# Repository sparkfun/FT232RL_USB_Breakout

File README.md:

FT232RL USB Breakout
====================

[
*FT232RL USB to Serial Breakout Board (BOB-00718)*](https://www.sparkfun.com/products/718)

This is a basic breakout board for FTDI's popular USB to UART IC.
VCCIO is tied to 3.3V through a solder jumper. 

Repository Contents
-------------------
* **/Hardware** - All Eagle design files (.brd, .sch)

License Information
-------------------
The hardware is released under [Creative Commons Share-alike 3.0](http://creativecommons.org/licenses/by-sa/3.0/).  
All other code is open source so please feel free to do anything you want with it; you buy me a beer if you use this and we meet someday ([Beerware license](http://en.wikipedia.org/wiki/Beerware)).

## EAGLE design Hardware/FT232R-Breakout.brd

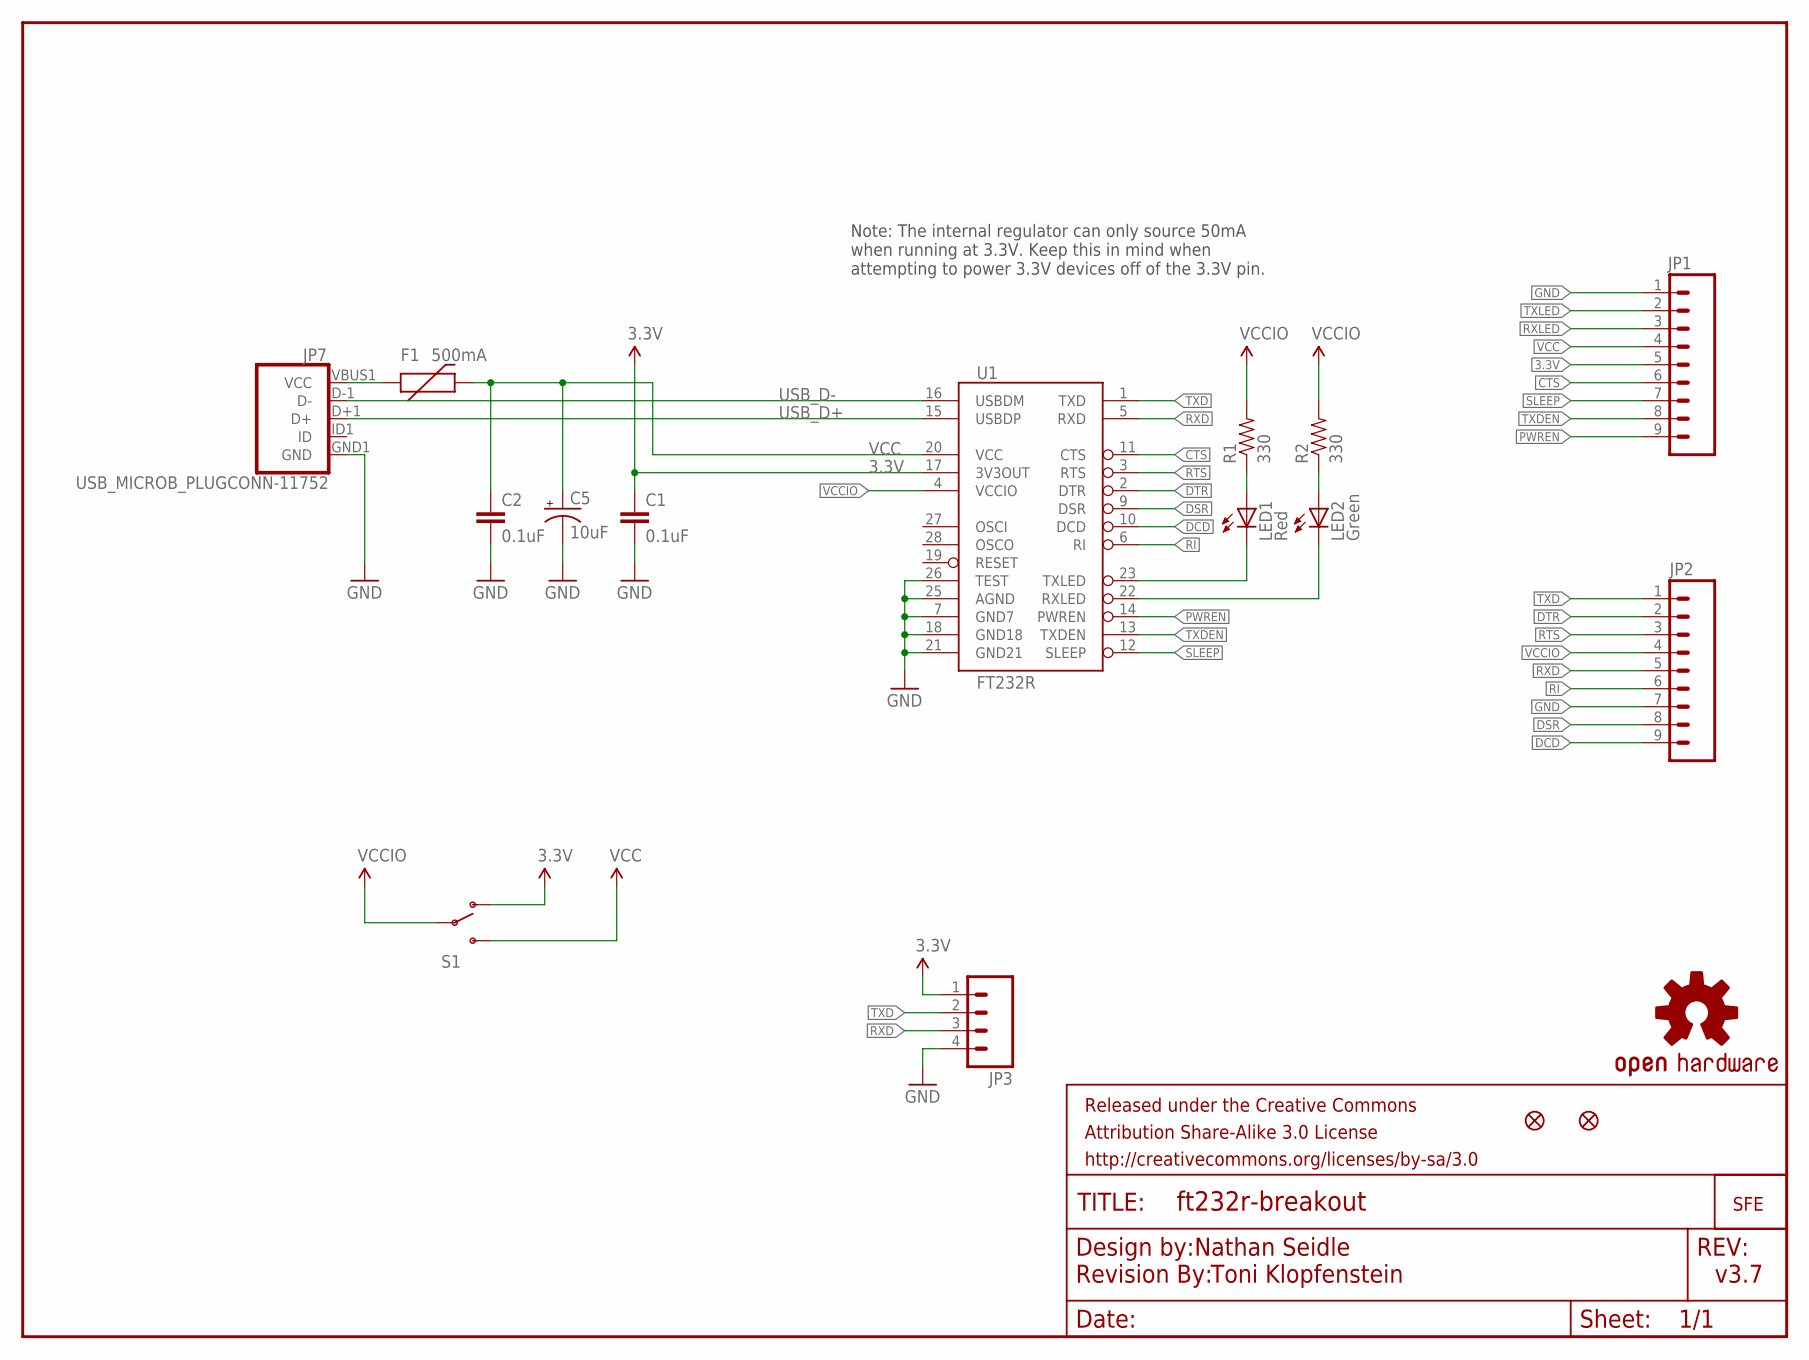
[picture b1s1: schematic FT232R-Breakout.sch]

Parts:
C1, C2: 0.1uF; 0603-CAP
C5: 10uF; EIA3216
F1: 500mA; PTC-1206
FRAME1: FRAME-LETTER; CREATIVE_COMMONS
JP1, JP2: M09; 1X09
JP3: M04PTH; 1X04
JP5, JP6: FIDUCIAL1X2; FIDUCIAL-1X2
JP7: USB_MICROB_PLUGCONN-11752; USB-B-MICRO-SMD_V03
LED1: Red; LED-0603
LED2: Green; LED-0603
LOGO1: OSHW-LOGOS; OSHW-LOGO-S
R1, R2: 330; 0603-RES
S1: SWITCH-SPDTSMD; AYZ0202
U1: FT232R; SSOP28DB
U$1: REVISION
U$2: LOGO-SFENEW; SFE-NEW-WEBLOGO

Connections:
3.3V: C1.1, JP1.5, JP3.1, S1.1 (O), U1.17 (3V3OUT)
CTS: JP1.6, U1.11 (CTS)
DCD: JP2.9, U1.10 (DCD)
DSR: JP2.8, U1.9 (DSR)
DTR: JP2.2, U1.2 (DTR)
GND: C1.2, C2.2, C5.C (-), JP1.1, JP2.7, JP3.4, JP7.GND1 (GND), U1.7 (GND7), U1.18 (GND18), U1.21 (GND21), U1.25 (AGND), U1.26 (TEST)
unnamed: LED1.A, R1.1
unnamed: LED2.A, R2.1
unnamed: F1.1, JP7.VBUS1 (VCC)
PWREN: JP1.9, U1.14 (PWREN)
RI: JP2.6, U1.6 (RI)
RTS: JP2.3, U1.3 (RTS)
RXD: JP2.5, JP3.3, U1.5 (RXD)
RXLED: JP1.3, LED2.C, U1.22 (RXLED)
SLEEP: JP1.7, U1.12 (SLEEP)
TXD: JP2.1, JP3.2, U1.1 (TXD)
TXDEN: JP1.8, U1.13 (TXDEN)
TXLED: JP1.2, LED1.C, U1.23 (TXLED)
USB_D+: JP7.D+1 (D+), U1.15 (USBDP)
USB_D-: JP7.D-1 (D-), U1.16 (USBDM)
VCC: C2.1, C5.A (+), F1.2, JP1.4, S1.3 (S), U1.20 (VCC)
VCCIO: JP2.4, R1.2, R2.2, S1.2, U1.4 (VCCIO)

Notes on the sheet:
v3.7
Nathan Seidle
Toni Klopfenstein
Note: The internal regulator can only source 50mA when running at 3.3V. Keep this in mind when attempting to power 3.3V devices off of the 3.3V pin.

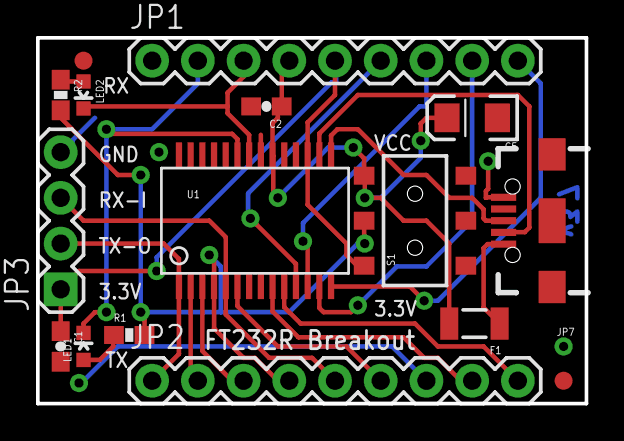
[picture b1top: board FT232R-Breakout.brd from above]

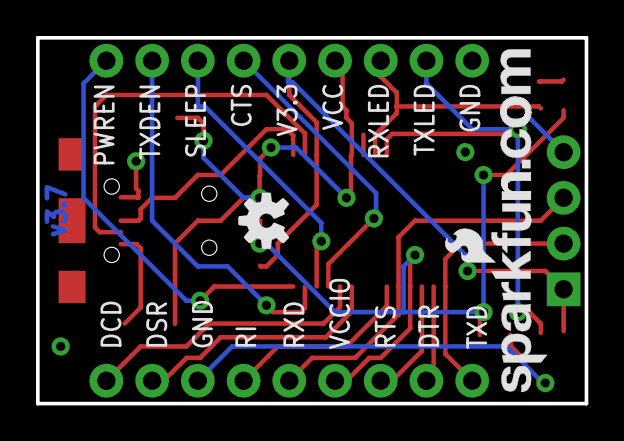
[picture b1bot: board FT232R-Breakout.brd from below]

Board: 2 copper layers, 30.5 x 20.3 mm, 20 parts (2 on the bottom side), 22 nets.

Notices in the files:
parts and their libraries:
SparkFun-Resistors: Licensing: CC v3.0 Share-Alike You are welcome to use this library for commercial purposes.
SparkFun-Aesthetics: Released under the Creative Commons Attribution Share-Alike 3.0 License
SparkFun-Aesthetics: Released under the Creative Commons
